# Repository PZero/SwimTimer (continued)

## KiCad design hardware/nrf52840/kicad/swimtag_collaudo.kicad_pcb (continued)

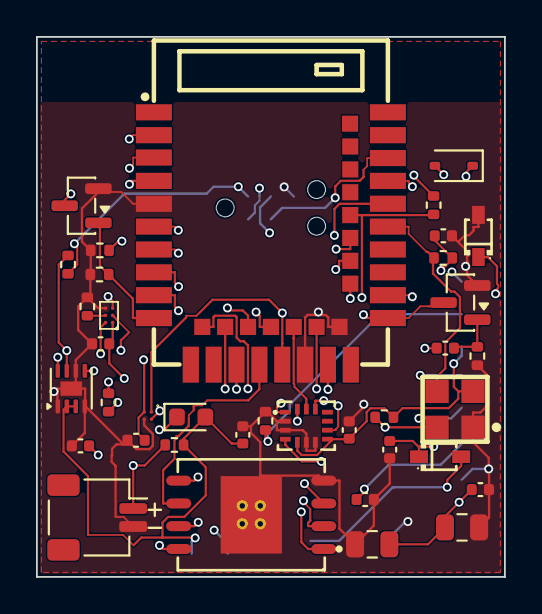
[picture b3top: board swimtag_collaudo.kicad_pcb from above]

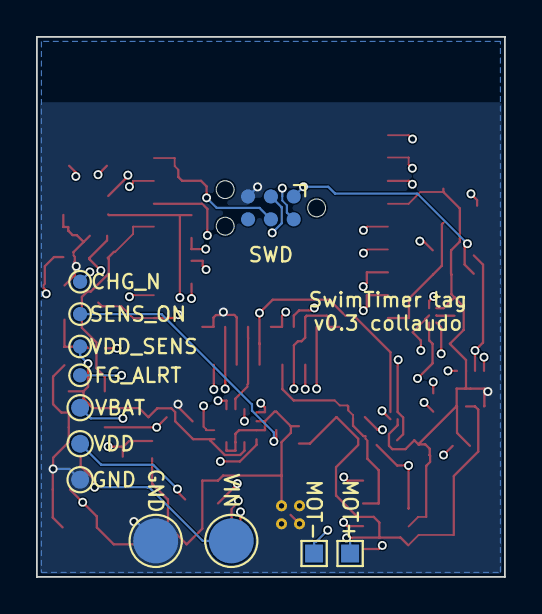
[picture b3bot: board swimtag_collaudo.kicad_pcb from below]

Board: 4 copper layers, 26.0 x 30.0 mm, 49 parts (12 on the bottom side), 36 nets.

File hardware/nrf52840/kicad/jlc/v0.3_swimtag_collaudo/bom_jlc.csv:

"Comment","Designator","Footprint","LCSC Part #","Quantity"
"10u","C1,C5,C7,C12","Capacitor_SMD:C_0402_1005Metric","C15525","4"
"100n","C2,C3,C4,C6,C8,C9","Capacitor_SMD:C_0402_1005Metric","C1525","6"
"47u","C10,C11","Capacitor_SMD:C_0805_2012Metric","C16780","2"
"1N4148WS","D1","Diode_SMD:D_SOD-323","C2128","1"
"rosso","D2","LED_SMD:LED_0603_1608Metric","C2286","1"
"SD05 TVS 5V","D3","swimtag:SOD-323_L1.8-W1.3-LS2.5-RD","C85201","1"
"B5819WS","D4","swimtag:SOD-323_L1.8-W1.3-LS2.5-RD","C22624","1"
"BATT JST-SH","J1","Connector_JST:JST_SH_SM02B-SRSS-TB_1x02-1MP_P1.00mm_Horizontal","C160402","1"
"AO3400A","Q1,Q2","Package_TO_SOT_SMD:SOT-23","C20917","2"
"10k","R1,R2,R5,R6,R9,R10","Resistor_SMD:R_0402_1005Metric","C25744","6"
"100k","R3","Resistor_SMD:R_0402_1005Metric","C25741","1"
"1k","R4","Resistor_SMD:R_0402_1005Metric","C11702","1"
"1M","R7,R8","Resistor_SMD:R_0402_1005Metric","C26083","2"
"0","R11","Resistor_SMD:R_0402_1005Metric","C17168","1"
"E73-2G4M08S1C","U1","swimtag:WIRELM-SMD_E73-2G4M08S1C","C356849","1"
"LSM6DSV16X","U2","swimtag:LGA-14_L3.0-W2.5-P0.50-BR","C5267406","1"
"W25Q256JVEIQ","U3","swimtag:WSON-8_L8.0-W6.10-P1.27-BL-EP","C97522","1"
"BQ25101","U4","swimtag:DSBGA-6_L0.9-W1.6-R2-C3-P0.40-BL","C478468","1"
"MS5837-02BA","U5","swimtag:LGA-4_L3.3-W3.3-P2.00-TL","C5785272","1"
"TPS22916C","U6","swimtag:DSBGA-4_L0.78-W0.78-P0.40","C2680319","1"
"MAX17048","U7","Package_DFN_QFN:TDFN-8-1EP_2x2mm_P0.5mm_EP0.8x1.2mm","C2682616","1"

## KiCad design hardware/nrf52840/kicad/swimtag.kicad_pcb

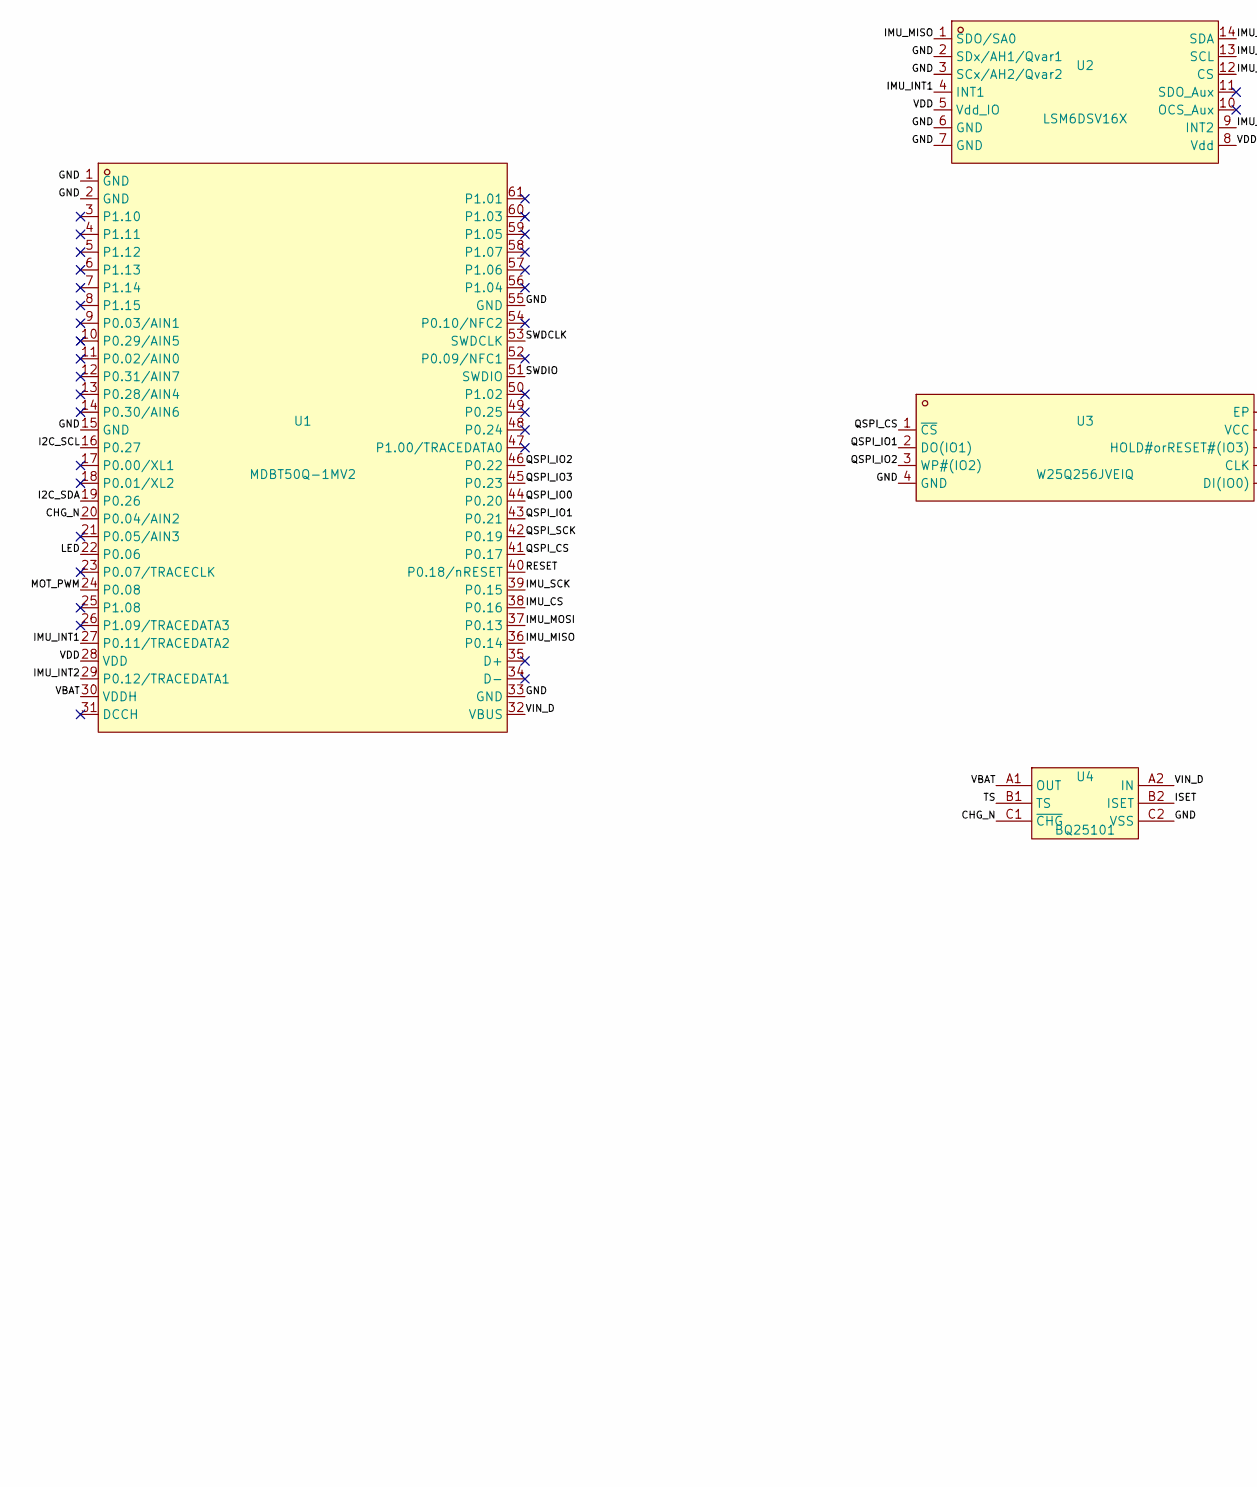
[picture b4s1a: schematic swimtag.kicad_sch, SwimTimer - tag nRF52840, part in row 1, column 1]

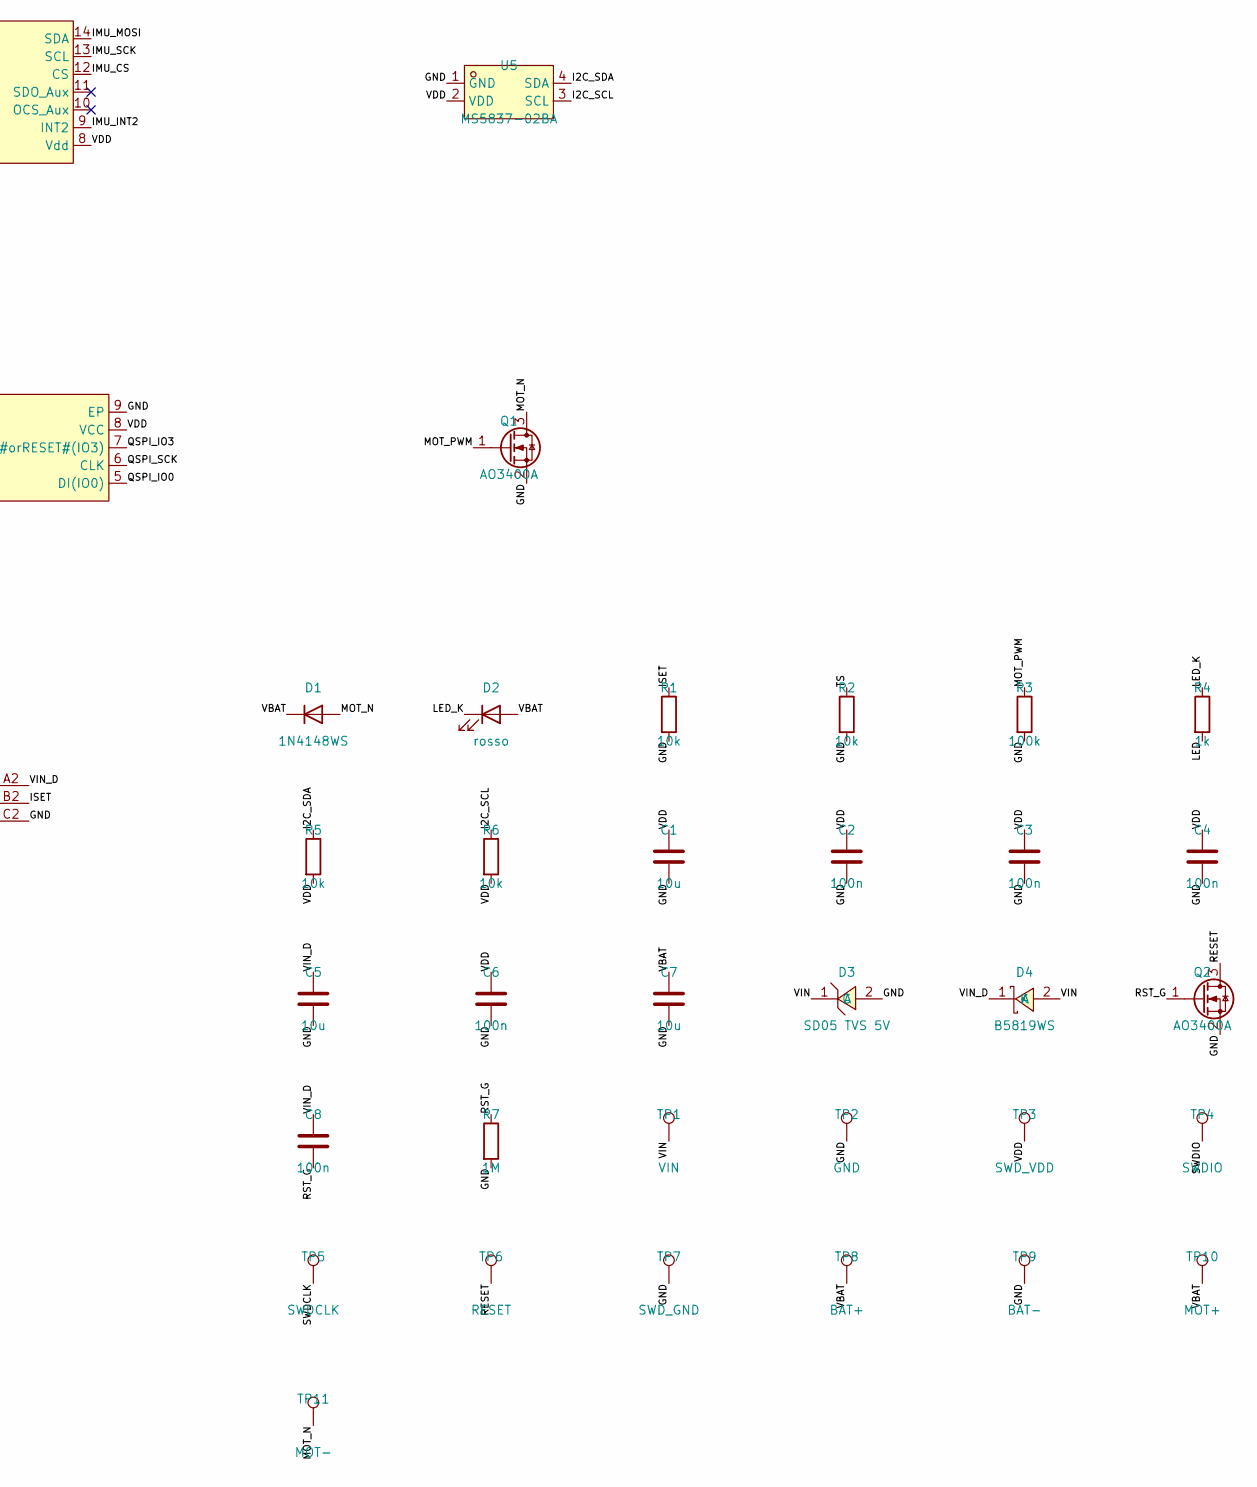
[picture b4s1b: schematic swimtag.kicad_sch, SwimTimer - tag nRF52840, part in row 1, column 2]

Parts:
C1, C5, C7: 10u; C_0402_1005Metric; LCSC C15525
C2, C3, C4, C6, C8: 100n; C_0402_1005Metric; LCSC C1525
D1: 1N4148WS; D_SOD-323; LCSC C2128
D2: rosso; LED_0603_1608Metric; LCSC C2286
D3: SD05 TVS 5V; SOD-323_L1.8-W1.3-LS2.5-RD; LCSC C85201
D4: B5819WS; SOD-323_L1.8-W1.3-LS2.5-RD; LCSC C22624
Q1, Q2: AO3400A; SOT-23; LCSC C20917
R1, R2, R5, R6: 10k; R_0402_1005Metric; LCSC C25744
R3: 100k; R_0402_1005Metric; LCSC C25741
R4: 1k; R_0402_1005Metric; LCSC C11702
R7: 1M; R_0402_1005Metric; LCSC C26083
TP1: VIN; TestPoint_Pad_D2.5mm
TP2: GND; TestPoint_Pad_D2.5mm
TP3: SWD_VDD; TestPoint_Pad_D1.0mm
TP4: SWDIO; TestPoint_Pad_D1.0mm
TP5: SWDCLK; TestPoint_Pad_D1.0mm
TP6: RESET; TestPoint_Pad_D1.0mm
TP7: SWD_GND; TestPoint_Pad_D1.0mm
TP8: BAT+; TestPoint_Pad_1.0x1.0mm
TP9: BAT-; TestPoint_Pad_1.0x1.0mm
TP10: MOT+; TestPoint_Pad_1.0x1.0mm
TP11: MOT-; TestPoint_Pad_1.0x1.0mm
U1: MDBT50Q-1MV2; COMM-SMD_MDBT50Q-1MV2-1; LCSC C5118826
U2: LSM6DSV16X; LGA-14_L3.0-W2.5-P0.50-BR; LCSC C5267406
U3: W25Q256JVEIQ; WSON-8_L8.0-W6.10-P1.27-BL-EP; LCSC C97522
U4: BQ25101; DSBGA-6_L0.9-W1.6-R2-C3-P0.40-BL; LCSC C478468
U5: MS5837-02BA; LGA-4_L3.3-W3.3-P2.00-TL; LCSC C2887129

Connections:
/CHG_N: U1.20 (P0.04/AIN2), U4.C1 (~CHG)
/GND: C1.2, C2.2, C3.2, C4.2, C5.2, C6.2, C7.2, D3.2 (A), Q1.2 (S), Q2.2 (S), R1.2, R2.2, R3.2, R7.2, TP2.1, TP7.1, TP9.1, U1.1 (GND), U1.2 (GND), U1.15 (GND), U1.33 (GND), U1.55 (GND), U2.2 (SDx/AH1/Qvar1), U2.3 (SCx/AH2/Qvar2), U2.6 (GND), U2.7 (GND), U3.4 (GND), U3.9 (EP), U4.C2 (VSS), U5.1 (GND)
/I2C_SCL: R6.1, U1.16 (P0.27), U5.3 (SCL)
/I2C_SDA: R5.1, U1.19 (P0.26), U5.4 (SDA)
/IMU_CS: U1.38 (P0.16), U2.12 (CS)
/IMU_INT1: U1.27 (P0.11/TRACEDATA2), U2.4 (INT1)
/IMU_INT2: U1.29 (P0.12/TRACEDATA1), U2.9 (INT2)
/IMU_MISO: U1.36 (P0.14), U2.1 (SDO/SA0)
/IMU_MOSI: U1.37 (P0.13), U2.14 (SDA)
/IMU_SCK: U1.39 (P0.15), U2.13 (SCL)
/ISET: R1.1, U4.B2 (ISET)
/LED: R4.2, U1.22 (P0.06)
/LED_K: D2.1 (K), R4.1
/MOT_N: D1.2 (A), Q1.3 (D), TP11.1
/MOT_PWM: Q1.1 (G), R3.1, U1.24 (P0.08)
/QSPI_CS: U1.41 (P0.17), U3.1 (~CS)
/QSPI_IO0: U1.44 (P0.20), U3.5 (DI(IO0))
/QSPI_IO1: U1.43 (P0.21), U3.2 (DO(IO1))
/QSPI_IO2: U1.46 (P0.22), U3.3 (WP#(IO2))
/QSPI_IO3: U1.45 (P0.23), U3.7 (HOLD#orRESET#(IO3))
/QSPI_SCK: U1.42 (P0.19), U3.6 (CLK)
/RESET: Q2.3 (D), TP6.1, U1.40 (P0.18/nRESET)
/RST_G: C8.2, Q2.1 (G), R7.1
/SWDCLK: TP5.1, U1.53 (SWDCLK)
/SWDIO: TP4.1, U1.51 (SWDIO)
/TS: R2.1, U4.B1 (TS)
/VBAT: C7.1, D1.1 (K), D2.2 (A), TP8.1, TP10.1, U1.30 (VDDH), U4.A1 (OUT)
/VDD: C1.1, C2.1, C3.1, C4.1, C6.1, R5.2, R6.2, TP3.1, U1.28 (VDD), U2.5 (Vdd_IO), U2.8 (Vdd), U3.8 (VCC), U5.2 (VDD)
/VIN: D3.1 (C), D4.2 (A), TP1.1
/VIN_D: C5.1, C8.1, D4.1 (K), U1.32 (VBUS), U4.A2 (IN)

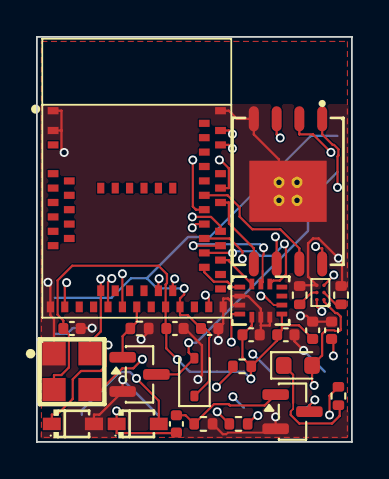
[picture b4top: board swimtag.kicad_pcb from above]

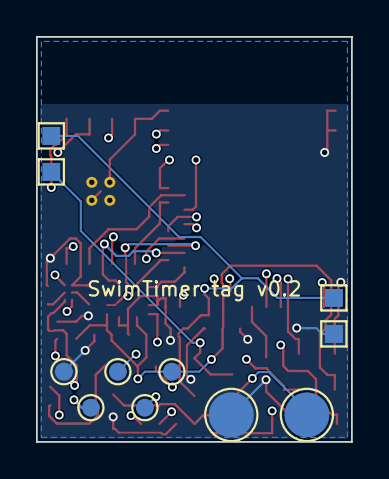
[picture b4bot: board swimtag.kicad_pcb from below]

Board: 4 copper layers, 17.5 x 22.5 mm, 37 parts (11 on the bottom side), 30 nets.

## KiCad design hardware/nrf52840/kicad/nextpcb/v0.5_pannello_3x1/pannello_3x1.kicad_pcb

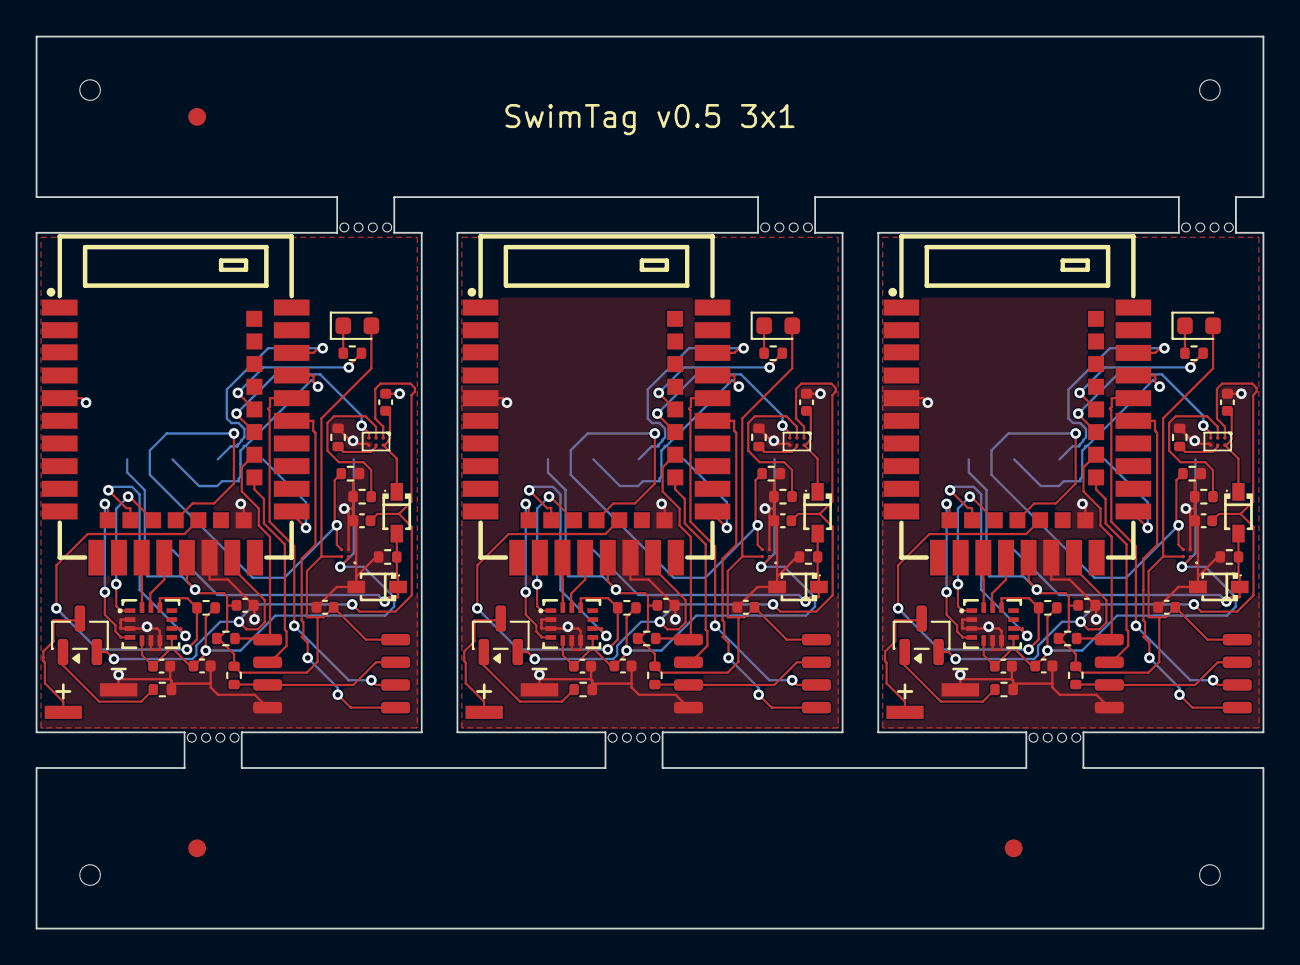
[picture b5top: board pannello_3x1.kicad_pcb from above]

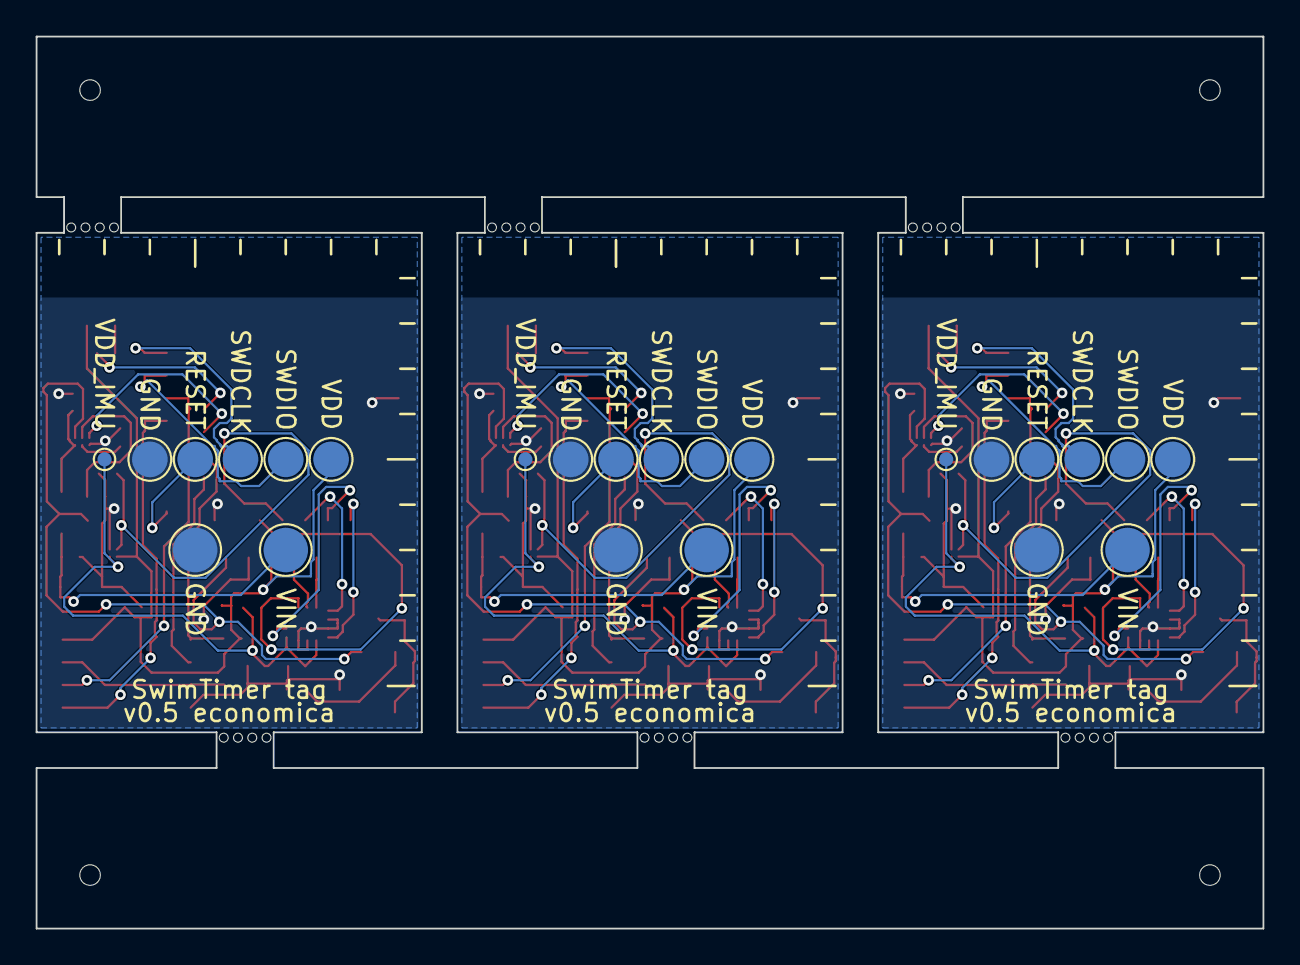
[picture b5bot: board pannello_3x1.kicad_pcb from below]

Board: 2 copper layers, 68.8 x 50.0 mm, 130 parts (24 on the bottom side), 84 nets.

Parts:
C1_1, C1_2, C1_3: 10u; C_0402_1005Metric
C2_1, C2_2, C2_3, C3_1, C3_2, C3_3, C4_1, C4_2, C4_3: 100n; C_0402_1005Metric
C5_1, C5_2, C5_3, C6_1, C6_2, C6_3: 4u7; C_0402_1005Metric
D1_1, D1_2, D1_3: rosso 0603; LED_0603_1608Metric
D2_1, D2_2, D2_3: 1N5819WS; SOD-323_L1.8-W1.3-LS2.5-RD
D3_1, D3_2, D3_3: PTVSLC3D5VB; SOD-323_L1.8-W1.3-LS2.5-RD
FID1, FID2, FID3: Fiducial_1mm_Mask2mm
J1_1, J1_2, J1_3: BATT header 1.27; HDR-SMD_2P-P1.27-V-M-LS4.2-R1
MB1, MB2, MB3, MB4, MB5, MB6, MB7, MB8, MB9, MB10, MB11, MB12, MB13, MB14, MB15, MB16, MB17, MB18, MB19, MB20, MB21, MB22, MB23, MB24: NPTH
Q1_1, Q1_2, Q1_3: AO3401A; SOT-23
R1_1, R1_2, R1_3, R2_1, R2_2, R2_3, R4_1, R4_2, R4_3: 10k; R_0402_1005Metric
R3_1, R3_2, R3_3: 1k; R_0402_1005Metric
R5_1, R5_2, R5_3, R6_1, R6_2, R6_3, R8_1, R8_2, R8_3, R9_1, R9_2, R9_3: 100k; R_0402_1005Metric
R7_1, R7_2, R7_3: 1M; R_0402_1005Metric
TH1, TH2, TH3, TH4: NPTH
TP1_1, TP1_2, TP1_3: VDD; TestPoint_Pad_D2.0mm_NoCY
TP2_1, TP2_2, TP2_3: SWDIO; TestPoint_Pad_D2.0mm_NoCY
TP3_1, TP3_2, TP3_3: SWDCLK; TestPoint_Pad_D2.0mm_NoCY
TP4_1, TP4_2, TP4_3: RESET; TestPoint_Pad_D2.0mm_NoCY
TP5_1, TP5_2, TP5_3: GND; TestPoint_Pad_D2.0mm_NoCY
TP6_1, TP6_2, TP6_3: VIN; TestPoint_Pad_D2.5mm
TP7_1, TP7_2, TP7_3: GND; TestPoint_Pad_D2.5mm
TP8_1, TP8_2, TP8_3: VDD_IMU; TestPoint_Pad_D0.8mm
U1_1, U1_2, U1_3: E73-2G4M08S1C; WIRELM-SMD_E73-2G4M08S1C
U2_1, U2_2, U2_3: LSM6DSV16X; LGA-14_L3.0-W2.5-P0.50-BR
U3_1, U3_2, U3_3: W25Q128JVSIQ; SOIC-8_5.3x5.3mm_P1.27mm
U4_1, U4_2, U4_3: BQ25101; DSBGA-6_L0.9-W1.6-R2-C3-P0.40-BL
U6_1, U6_2, U6_3: TPS22916C; DSBGA-4_L0.78-W0.78-P0.40

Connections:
B1_/BAT_G: Q1_1.1, R9_1.1
B1_/BAT_IN: J1_1.1, Q1_1.3
B1_/CHG_N: U1_1.32, U4_1.C1
B1_/FL_CS: R5_1.1, U1_1.30, U3_1.1
B1_/FL_IO23: R4_1.1, U3_1.3, U3_1.7
B1_/FL_MISO: U1_1.28, U3_1.2
B1_/FL_MOSI: U1_1.33, U3_1.5
B1_/FL_SCK: U1_1.35, U3_1.6
B1_/GND: C1_1.2, C2_1.2, C3_1.2, C4_1.2, C5_1.2, C6_1.2, D3_1.2, J1_1.2, R1_1.2, R2_1.2, R7_1.2, R8_1.2, R9_1.2, TP5_1.1, TP7_1.1, U1_1.5, U1_1.21, U1_1.24, U2_1.2, U2_1.3, U2_1.6, U2_1.7, U3_1.4, U4_1.C2, U6_1.B1
B1_/IMU_CS: R6_1.1, U1_1.20, U2_1.12
B1_/IMU_INT1: U1_1.12, U2_1.4
B1_/IMU_INT2: U1_1.14, U2_1.9
B1_/IMU_MISO: U1_1.16, U2_1.1
B1_/IMU_MOSI: U1_1.15, U2_1.14
B1_/IMU_SCK: U1_1.17, U2_1.13
B1_/ISET: R1_1.1, U4_1.B2
B1_/LED: R3_1.2, U1_1.34
B1_/LED_K: D1_1.1, R3_1.1
B1_/RESET: TP4_1.1, U1_1.26
B1_/SENS_ON: R7_1.1, U1_1.18, U6_1.B2
B1_/SWDCLK: TP3_1.1, U1_1.39
B1_/SWDIO: TP2_1.1, U1_1.37
B1_/TS: R2_1.1, U4_1.B1
B1_/VBAT: C6_1.1, Q1_1.2, U1_1.23, U4_1.A1
B1_/VDD: C1_1.1, C3_1.1, D1_1.2, R4_1.2, R5_1.2, TP1_1.1, U1_1.19, U3_1.8, U6_1.A2
B1_/VDD_IMU: C2_1.1, C4_1.1, R6_1.2, TP8_1.1, U2_1.5, U2_1.8, U6_1.A1
B1_/VIN: D2_1.2, D3_1.1, R8_1.1, TP6_1.1
B1_/VIN_D: C5_1.1, D2_1.1, U4_1.A2
B2_/BAT_G: Q1_2.1, R9_2.1
B2_/BAT_IN: J1_2.1, Q1_2.3
B2_/CHG_N: U1_2.32, U4_2.C1
B2_/FL_CS: R5_2.1, U1_2.30, U3_2.1
B2_/FL_IO23: R4_2.1, U3_2.3, U3_2.7
B2_/FL_MISO: U1_2.28, U3_2.2
B2_/FL_MOSI: U1_2.33, U3_2.5
B2_/FL_SCK: U1_2.35, U3_2.6
B2_/GND: C1_2.2, C2_2.2, C3_2.2, C4_2.2, C5_2.2, C6_2.2, D3_2.2, J1_2.2, R1_2.2, R2_2.2, R7_2.2, R8_2.2, R9_2.2, TP5_2.1, TP7_2.1, U1_2.5, U1_2.21, U1_2.24, U2_2.2, U2_2.3, U2_2.6, U2_2.7, U3_2.4, U4_2.C2, U6_2.B1
B2_/IMU_CS: R6_2.1, U1_2.20, U2_2.12
B2_/IMU_INT1: U1_2.12, U2_2.4
B2_/IMU_INT2: U1_2.14, U2_2.9
B2_/IMU_MISO: U1_2.16, U2_2.1
B2_/IMU_MOSI: U1_2.15, U2_2.14
B2_/IMU_SCK: U1_2.17, U2_2.13
B2_/ISET: R1_2.1, U4_2.B2
B2_/LED: R3_2.2, U1_2.34
B2_/LED_K: D1_2.1, R3_2.1
B2_/RESET: TP4_2.1, U1_2.26
B2_/SENS_ON: R7_2.1, U1_2.18, U6_2.B2
B2_/SWDCLK: TP3_2.1, U1_2.39
B2_/SWDIO: TP2_2.1, U1_2.37
B2_/TS: R2_2.1, U4_2.B1
B2_/VBAT: C6_2.1, Q1_2.2, U1_2.23, U4_2.A1
B2_/VDD: C1_2.1, C3_2.1, D1_2.2, R4_2.2, R5_2.2, TP1_2.1, U1_2.19, U3_2.8, U6_2.A2
B2_/VDD_IMU: C2_2.1, C4_2.1, R6_2.2, TP8_2.1, U2_2.5, U2_2.8, U6_2.A1
B2_/VIN: D2_2.2, D3_2.1, R8_2.1, TP6_2.1
B2_/VIN_D: C5_2.1, D2_2.1, U4_2.A2
B3_/BAT_G: Q1_3.1, R9_3.1
B3_/BAT_IN: J1_3.1, Q1_3.3
B3_/CHG_N: U1_3.32, U4_3.C1
B3_/FL_CS: R5_3.1, U1_3.30, U3_3.1
B3_/FL_IO23: R4_3.1, U3_3.3, U3_3.7
B3_/FL_MISO: U1_3.28, U3_3.2
B3_/FL_MOSI: U1_3.33, U3_3.5
B3_/FL_SCK: U1_3.35, U3_3.6
B3_/GND: C1_3.2, C2_3.2, C3_3.2, C4_3.2, C5_3.2, C6_3.2, D3_3.2, J1_3.2, R1_3.2, R2_3.2, R7_3.2, R8_3.2, R9_3.2, TP5_3.1, TP7_3.1, U1_3.5, U1_3.21, U1_3.24, U2_3.2, U2_3.3, U2_3.6, U2_3.7, U3_3.4, U4_3.C2, U6_3.B1
B3_/IMU_CS: R6_3.1, U1_3.20, U2_3.12
B3_/IMU_INT1: U1_3.12, U2_3.4
B3_/IMU_INT2: U1_3.14, U2_3.9
B3_/IMU_MISO: U1_3.16, U2_3.1
B3_/IMU_MOSI: U1_3.15, U2_3.14
B3_/IMU_SCK: U1_3.17, U2_3.13
B3_/ISET: R1_3.1, U4_3.B2
B3_/LED: R3_3.2, U1_3.34
B3_/LED_K: D1_3.1, R3_3.1
B3_/RESET: TP4_3.1, U1_3.26
B3_/SENS_ON: R7_3.1, U1_3.18, U6_3.B2
B3_/SWDCLK: TP3_3.1, U1_3.39
B3_/SWDIO: TP2_3.1, U1_3.37
B3_/TS: R2_3.1, U4_3.B1
B3_/VBAT: C6_3.1, Q1_3.2, U1_3.23, U4_3.A1
B3_/VDD: C1_3.1, C3_3.1, D1_3.2, R4_3.2, R5_3.2, TP1_3.1, U1_3.19, U3_3.8, U6_3.A2
B3_/VDD_IMU: C2_3.1, C4_3.1, R6_3.2, TP8_3.1, U2_3.5, U2_3.8, U6_3.A1
B3_/VIN: D2_3.2, D3_3.1, R8_3.1, TP6_3.1
B3_/VIN_D: C5_3.1, D2_3.1, U4_3.A2
